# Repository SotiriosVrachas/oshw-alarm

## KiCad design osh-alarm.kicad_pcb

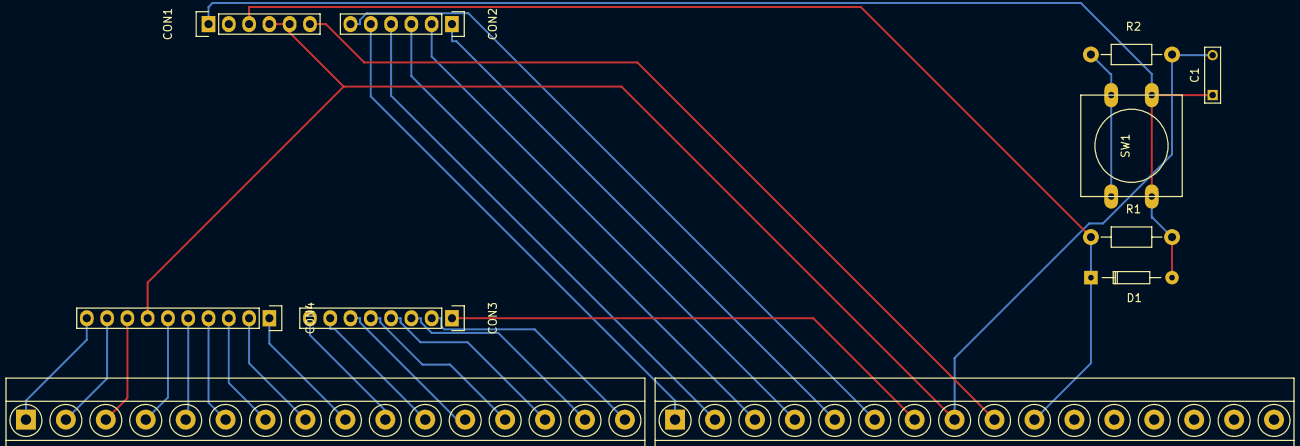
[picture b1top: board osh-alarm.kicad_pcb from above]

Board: 2 copper layers, 11 parts (0 on the bottom side), 28 nets.

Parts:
C1: C; C_Rect_L7_W2_P5
CON1, CON2: CONN_01X06; Pin_Header_Straight_1x06
CON3: CONN_01X08; Pin_Header_Straight_1x08
CON4: CONN_01X10; Pin_Header_Straight_1x10
D1: D_Schottky; Diode_DO-35_SOD27_Horizontal_RM10
P1, P2: CONN_01X16; TerminalBlock_Pheonix_MKDS1.5-16pol
R1, R2: R; Resistor_Horizontal_RM10mm
SW1: SW_PUSH; SW_PUSH-12mm

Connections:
+5V: CON1.3, D1.1, P1.10, R1.1
+12V: CON1.6, P1.9
GND: C1.2, CON1.4, CON1.5, CON4.7, P1.8, R2.2
unnamed: C1.1, CON1.1, D1.2, R1.2, SW1.2
unnamed: CON2.1, P1.5
unnamed: CON2.2, P1.4
unnamed: CON2.3, P1.3
unnamed: CON2.4, P1.2
unnamed: CON2.5, P1.1
unnamed: CON2.6, P1.6
unnamed: CON3.1, P1.7
unnamed: CON3.2, P2.16
unnamed: CON3.3, P2.15
unnamed: CON3.4, P2.14
unnamed: CON3.5, P2.13
unnamed: CON3.6, P2.12
unnamed: CON3.7, P2.11
unnamed: CON3.8, P2.10
unnamed: CON4.1, P2.9
unnamed: CON4.2, P2.8
unnamed: CON4.3, P2.7
unnamed: CON4.4, P2.6
unnamed: CON4.5, P2.5
unnamed: CON4.6, P2.4
unnamed: CON4.8, P2.3
unnamed: CON4.9, P2.2
unnamed: CON4.10, P2.1
unnamed: R2.1, SW1.1

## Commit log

2016-10-11 init
